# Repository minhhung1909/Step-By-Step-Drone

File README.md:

### 🚀 Day 1: Power Management Architecture & Schematic Design
* **Fixed & Verified Output Rails**: Finalized the power tree architecture for the 4-in-1 FOC ESC[cite: 1].
* **Buck Converter Stage (MP2359)**: Configured the step-down regulator to efficiently drop the main battery voltage down to a stable 5V rail.
* **LDO Linear Regulator Stage (MIC5219-3.3)**: Integrated the ultra-low noise LDO to convert 5V to 3.3V, ensuring a clean analog supply (`VDDA`) for the STM32G431 MCU and preventing FOC current-sensing noise.
* **Schematic Captures**: 
  * Configured proper bootstrapping components and decoupling/filtering capacitors.
  * Set up component attributes (such as DNP for optional feed-forward configurations) to keep the BOM clean for manufacturing.

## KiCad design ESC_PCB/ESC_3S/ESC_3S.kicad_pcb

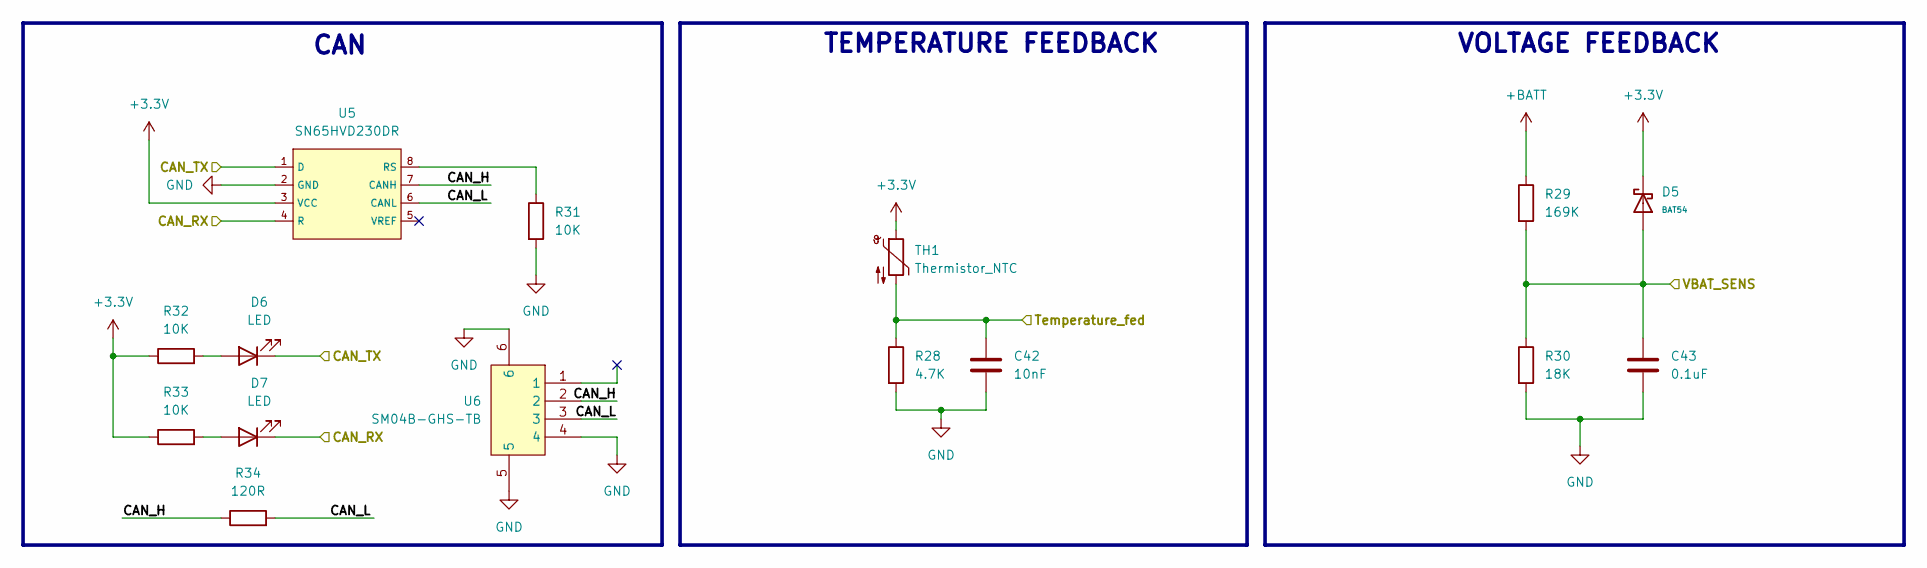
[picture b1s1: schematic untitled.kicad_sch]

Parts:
C42: 10nF; C_0603_1608Metric_Pad1.08x0.95mm_HandSolder
C43: 0.1uF; C_0603_1608Metric_Pad1.08x0.95mm_HandSolder
D5: BAT54; D_SOT-23; Part BAT54; LCSC C22466368
D6, D7: LED; LED_0603_1608Metric_Pad1.05x0.95mm_HandSolder
R28: 4.7K; R_0603_1608Metric_Pad0.98x0.95mm_HandSolder
R29: 169K; R_0603_1608Metric_Pad0.98x0.95mm_HandSolder
R30: 18K; R_0603_1608Metric_Pad0.98x0.95mm_HandSolder
R31, R32, R33: 10K; R_0603_1608Metric_Pad0.98x0.95mm_HandSolder
R34: 120R; R_0603_1608Metric_Pad0.98x0.95mm_HandSolder
TH1: Thermistor_NTC; R_Axial_DIN0204_L3.6mm_D1.6mm_P2.54mm_Vertical
U5: SN65HVD230DR; SOIC-8_L4.9-W3.9-P1.27-LS6.0-BL; Supply Voltage 3V~3.6V; Part SN65HVD230DR; LCSC C12084
U6: SM04B-GHS-TB; CONN-SMD_4P-P1.25_SM04B-GHS-TB-LF-SN; MPN SM04B-GHS-TB(LF)(SN); LCSC Part C189895

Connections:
+3.3V: D5.3, R32.1, R33.1, TH1.1, U5.3 (VCC); also elsewhere on the board
+BATT: R29.1; also elsewhere on the board
/Addition/CAN_H: R34.1, U5.7 (CANH), U6.2
/Addition/CAN_L: R34.2, U5.6 (CANL), U6.3
/Addition/CAN_RX: D7.1 (K), U5.4 (R); also elsewhere on the board
/Addition/CAN_TX: D6.1 (K), U5.1 (D); also elsewhere on the board
/Addition/Temperature_fed: C42.1, R28.1, TH1.2; also elsewhere on the board
/Addition/VBAT_SENS: C43.1, D5.1, R29.2, R30.1; also elsewhere on the board
GND: C42.2, C43.2, R28.2, R30.2, R31.2, U5.2 (GND), U6.4, U6.5, U6.6; also elsewhere on the board
unnamed: D6.2 (A), R32.2
unnamed: D7.2 (A), R33.2
unnamed: R31.1, U5.8 (RS)

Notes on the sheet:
VOLTAGE FEEDBACK
TEMPERATURE FEEDBACK
CAN

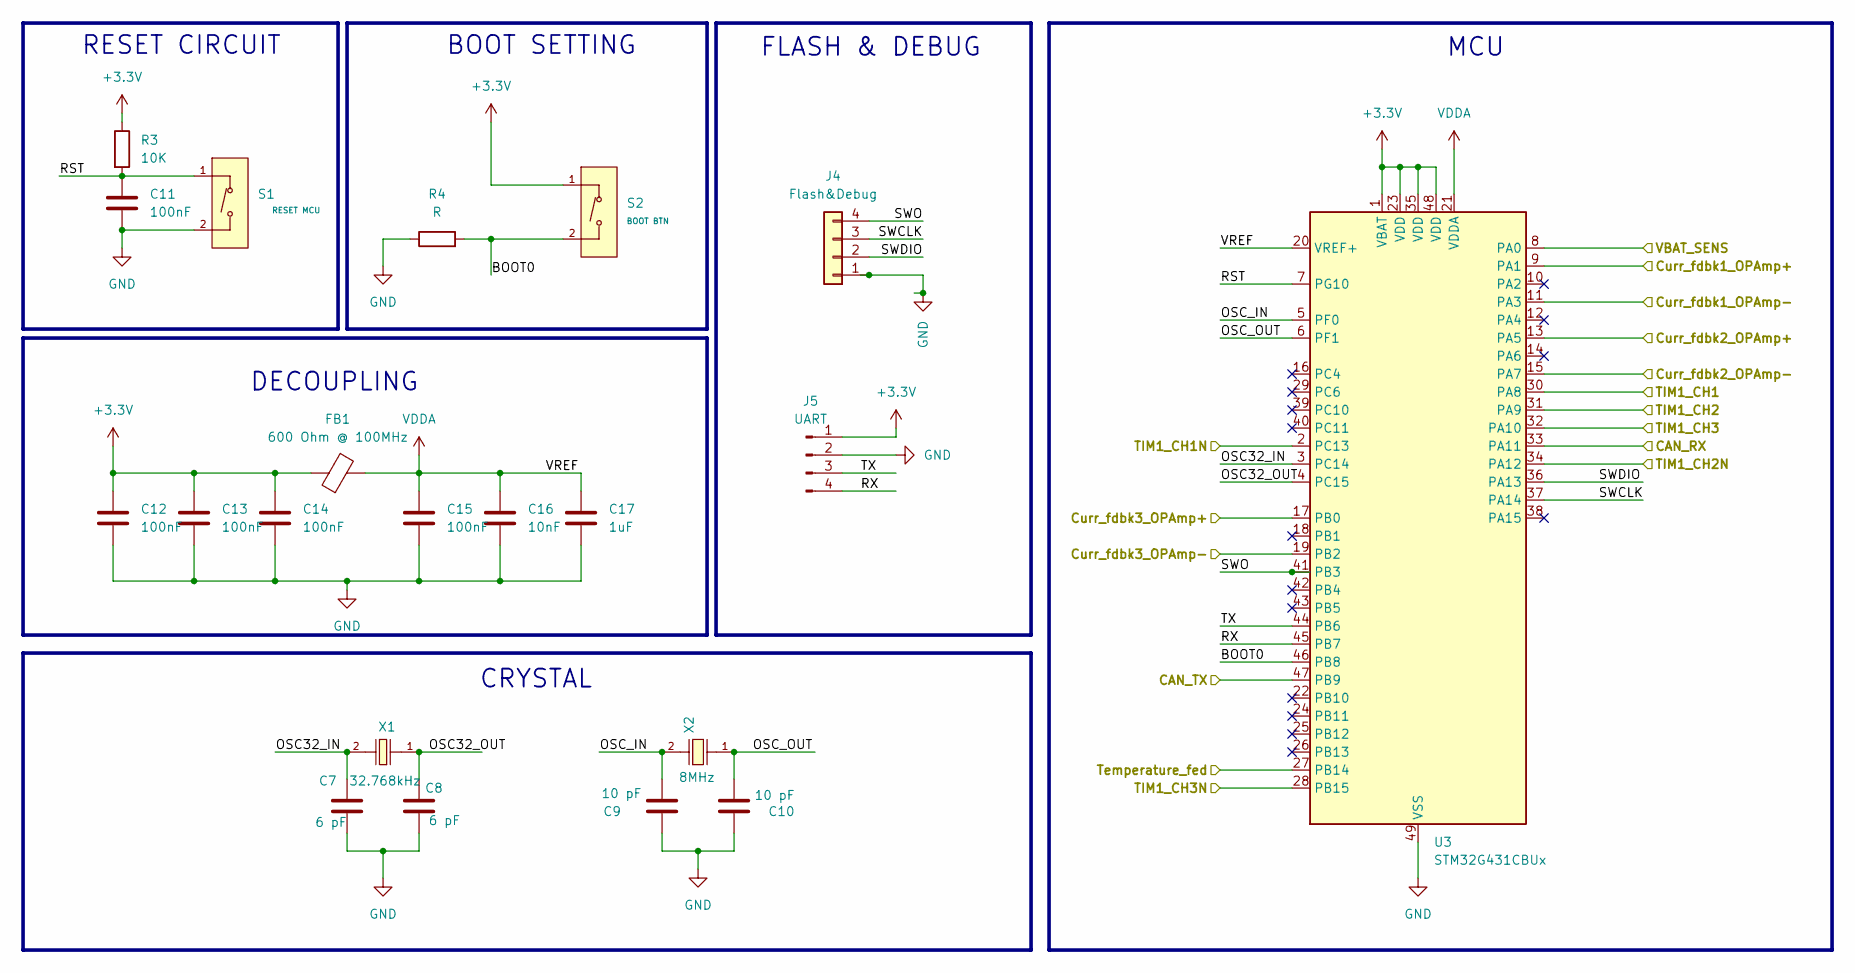
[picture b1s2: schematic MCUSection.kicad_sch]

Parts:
C7, C8: 6 pF; C_0603_1608Metric_Pad1.08x0.95mm_HandSolder
C9, C10: 10 pF; C_0603_1608Metric_Pad1.08x0.95mm_HandSolder
C11, C12, C13, C14, C15: 100nF; C_0603_1608Metric_Pad1.08x0.95mm_HandSolder
C16: 10nF; C_0603_1608Metric_Pad1.08x0.95mm_HandSolder
C17: 1uF; C_0603_1608Metric_Pad1.08x0.95mm_HandSolder
FB1: 600 Ohm @ 100MHz; L_0603_1608Metric_Pad1.05x0.95mm_HandSolder
J4: Flash&Debug; PinHeader_1x04_P1.27mm_Vertical
J5: UART; PinHeader_1x04_P2.54mm_Vertical
R3: 10K; R_0603_1608Metric_Pad0.98x0.95mm_HandSolder
R4: R; R_0603_1608Metric_Pad0.98x0.95mm_HandSolder
S1: RESET MCU; SW_TS-1088-AR02016; Voltage Rating (Dc) 12V; Part TS-1088-AR02016; LCSC C720477
S2: BOOT BTN; SW_TS-1088-AR02016; Voltage Rating (Dc) 12V; Part TS-1088-AR02016; LCSC C720477
U3: STM32G431CBUx; QFN-48-1EP_7x7mm_P0.5mm_EP5.6x5.6mm
X1: Q13FC1350000400; FC-135R_L3.2-W1.5; Frequency Tolerance ±20ppm; Part Q13FC13500004; LCSC C32346
X2: X50328MSB2GI; CRYSTAL-SMD_L5.0-W3.2; Frequency Tolerance ±10ppm; Part X50328MSB2GI; LCSC C115962

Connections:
+3.3V: C12.1, C13.1, C14.1, FB1.1, J5.1, R3.1, S2.1 (A), U3.1 (VBAT), U3.23 (VDD), U3.35 (VDD), U3.48 (VDD); also elsewhere on the board
/Addition/CAN_RX: U3.33 (PA11); also elsewhere on the board
/Addition/CAN_TX: U3.47 (PB9); also elsewhere on the board
/Addition/Temperature_fed: U3.27 (PB14); also elsewhere on the board
/Addition/VBAT_SENS: U3.8 (PA0); also elsewhere on the board
/Gate Driver and 3PH Inverter Bridge/Curr_fdbk1_OPAmp+: U3.9 (PA1); also elsewhere on the board
/Gate Driver and 3PH Inverter Bridge/Curr_fdbk2_OPAmp+: U3.13 (PA5); also elsewhere on the board
/Gate Driver and 3PH Inverter Bridge/Curr_fdbk3_OPAmp+: U3.17 (PB0); also elsewhere on the board
/Gate Driver and 3PH Inverter Bridge/TIM1_CH1: U3.30 (PA8); also elsewhere on the board
/Gate Driver and 3PH Inverter Bridge/TIM1_CH1N: U3.2 (PC13); also elsewhere on the board
/Gate Driver and 3PH Inverter Bridge/TIM1_CH2: U3.31 (PA9); also elsewhere on the board
/Gate Driver and 3PH Inverter Bridge/TIM1_CH2N: U3.34 (PA12); also elsewhere on the board
/Gate Driver and 3PH Inverter Bridge/TIM1_CH3: U3.32 (PA10); also elsewhere on the board
/Gate Driver and 3PH Inverter Bridge/TIM1_CH3N: U3.28 (PB15); also elsewhere on the board
/Gate Driver and 3PH Inverter Bridge/V_Shunt_1-: U3.11 (PA3); also elsewhere on the board
/Gate Driver and 3PH Inverter Bridge/V_Shunt_2-: U3.15 (PA7); also elsewhere on the board
/Gate Driver and 3PH Inverter Bridge/V_Shunt_3-: U3.19 (PB2); also elsewhere on the board
/MCU Section/BOOT0: R4.2, S2.2 (B), U3.46 (PB8)
/MCU Section/OSC32_IN: C7.1, U3.3 (PC14), X1.2
/MCU Section/OSC32_OUT: C8.1, U3.4 (PC15), X1.1
/MCU Section/OSC_IN: C9.1, U3.5 (PF0), X2.2
/MCU Section/OSC_OUT: C10.1, U3.6 (PF1), X2.1
/MCU Section/RST: C11.1, R3.2, S1.1 (A), U3.7 (PG10)
/MCU Section/RX: J5.4, U3.45 (PB7); also elsewhere on the board
/MCU Section/SWCLK: J4.3, U3.37 (PA14); also elsewhere on the board
/MCU Section/SWDIO: J4.2, U3.36 (PA13); also elsewhere on the board
/MCU Section/SWO: J4.4, U3.41 (PB3); also elsewhere on the board
/MCU Section/TX: J5.3, U3.44 (PB6); also elsewhere on the board
GND: C7.2, C8.2, C9.2, C10.2, C11.2, C12.2, C13.2, C14.2, C15.2, C16.2, C17.2, J4.1, J5.2, R4.1, S1.2 (B), U3.49 (VSS); also elsewhere on the board
VDDA: C15.1, C16.1, C17.1, FB1.2, U3.20 (VREF+), U3.21 (VDDA)

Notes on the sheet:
FLASH & DEBUG
DECOUPLING
RESET CIRCUIT
BOOT SETTING
CRYSTAL
MCU

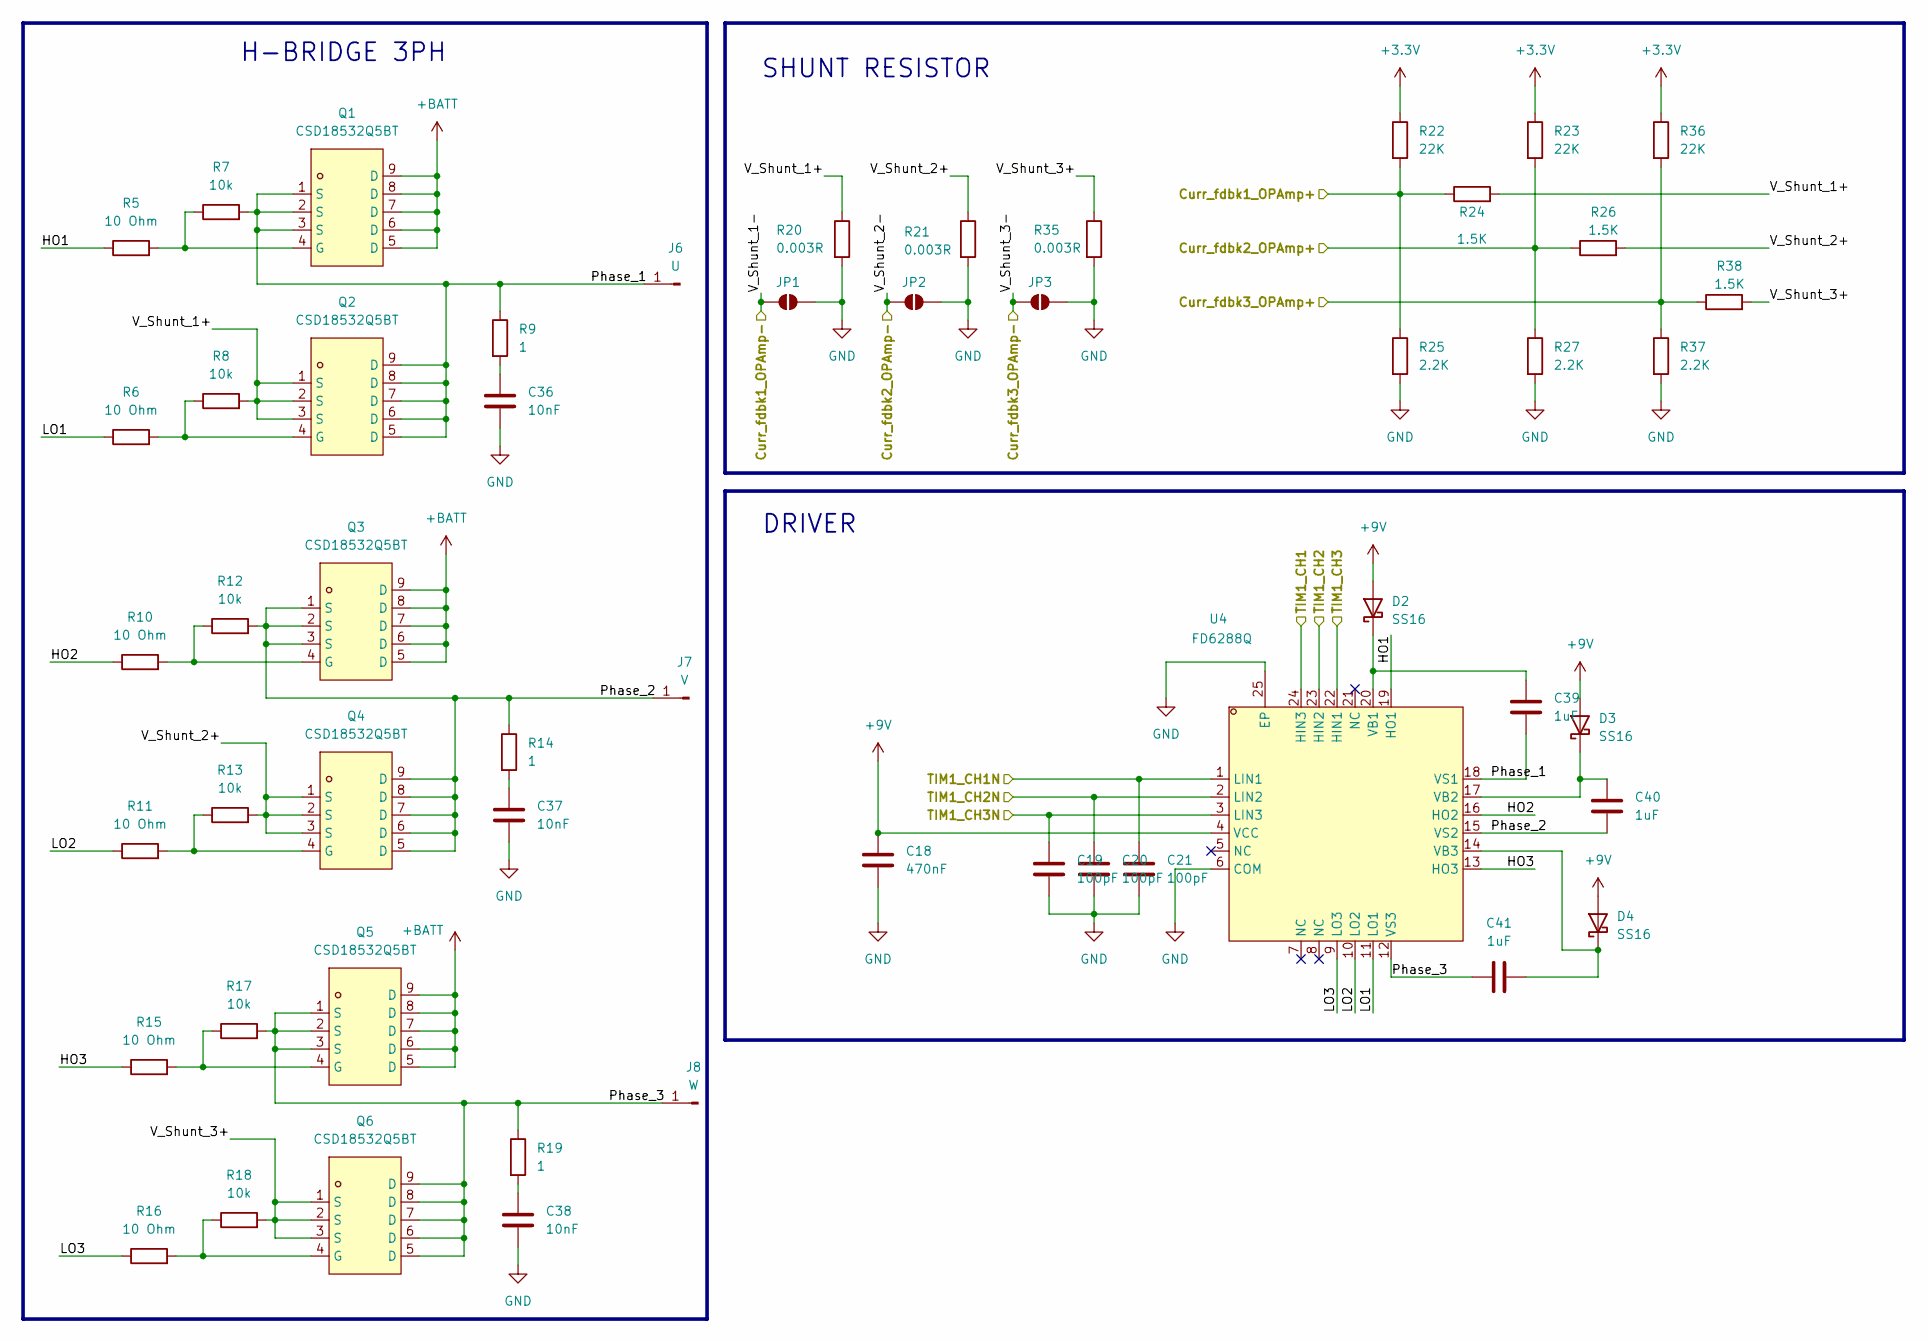
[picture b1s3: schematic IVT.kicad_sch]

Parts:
C18: 470nF; C_0603_1608Metric_Pad1.08x0.95mm_HandSolder
C19, C20, C21: 100pF; C_0603_1608Metric_Pad1.08x0.95mm_HandSolder
C36, C37, C38: 10nF; C_0603_1608Metric_Pad1.08x0.95mm_HandSolder
C39, C40, C41: 1uF; C_0603_1608Metric_Pad1.08x0.95mm_HandSolder
D2, D3, D4: SS16; D_SMA
J6: U; SolderWirePad_1x01_SMD_1x2mm
J7: V; SolderWirePad_1x01_SMD_1x2mm
J8: W; SolderWirePad_1x01_SMD_1x2mm
JP1, JP2, JP3: SolderJumper_2_Open; R_0402_1005Metric
Q1, Q2, Q3, Q4, Q5, Q6: CSD18532Q5BT; SON-8_L5.0-W6.0-P1.27-BL-1; MPN CSD18532Q5BT; LCSC Part C2876541
R5, R6, R10, R11, R15, R16: 10 Ohm; R_0603_1608Metric_Pad0.98x0.95mm_HandSolder
R7, R8, R12, R13, R17, R18: 10k; R_0603_1608Metric_Pad0.98x0.95mm_HandSolder
R9, R14, R19: 1; R_0603_1608Metric_Pad0.98x0.95mm_HandSolder
R20, R21, R35: 0.003R; R_2512_6332Metric_Pad1.40x3.35mm_HandSolder
R22, R23, R36: 22K; R_0603_1608Metric_Pad0.98x0.95mm_HandSolder
R24, R26, R38: 1.5K; R_0603_1608Metric_Pad0.98x0.95mm_HandSolder
R25, R27, R37: 2.2K; R_0603_1608Metric_Pad0.98x0.95mm_HandSolder
U4: FD6288Q; QFN-24_L4.0-W4.0-P0.50-BL-EP2.6; MPN FD6288Q; LCSC Part C328453

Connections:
+3.3V: R22.1, R23.1, R36.1; also elsewhere on the board
+9V: C18.1, D2.2 (A), D3.2 (A), D4.2 (A), U4.4 (VCC); also elsewhere on the board
+BATT: Q1.5 (D), Q1.6 (D), Q1.7 (D), Q1.8 (D), Q1.9 (D), Q3.5 (D), Q3.6 (D), Q3.7 (D), Q3.8 (D), Q3.9 (D), Q5.5 (D), Q5.6 (D), Q5.7 (D), Q5.8 (D), Q5.9 (D); also elsewhere on the board
/Gate Driver and 3PH Inverter Bridge/Curr_fdbk1_OPAmp+: R22.2, R24.1, R25.1; also elsewhere on the board
/Gate Driver and 3PH Inverter Bridge/Curr_fdbk2_OPAmp+: R23.2, R26.1, R27.1; also elsewhere on the board
/Gate Driver and 3PH Inverter Bridge/Curr_fdbk3_OPAmp+: R36.2, R37.1, R38.1; also elsewhere on the board
/Gate Driver and 3PH Inverter Bridge/HO1: R5.1, U4.19 (HO1)
/Gate Driver and 3PH Inverter Bridge/HO2: R10.1, U4.16 (HO2)
/Gate Driver and 3PH Inverter Bridge/HO3: R15.1, U4.13 (HO3)
/Gate Driver and 3PH Inverter Bridge/LO1: R6.1, U4.11 (LO1)
/Gate Driver and 3PH Inverter Bridge/LO2: R11.1, U4.10 (LO2)
/Gate Driver and 3PH Inverter Bridge/LO3: R16.1, U4.9 (LO3)
/Gate Driver and 3PH Inverter Bridge/Phase_1: C39.2, J6.1, Q1.1 (S), Q1.2 (S), Q1.3 (S), Q2.5 (D), Q2.6 (D), Q2.7 (D), Q2.8 (D), Q2.9 (D), R7.2, R9.1, U4.18 (VS1)
/Gate Driver and 3PH Inverter Bridge/Phase_2: C40.2, J7.1, Q3.1 (S), Q3.2 (S), Q3.3 (S), Q4.5 (D), Q4.6 (D), Q4.7 (D), Q4.8 (D), Q4.9 (D), R12.2, R14.1, U4.15 (VS2)
/Gate Driver and 3PH Inverter Bridge/Phase_3: C41.1, J8.1, Q5.1 (S), Q5.2 (S), Q5.3 (S), Q6.5 (D), Q6.6 (D), Q6.7 (D), Q6.8 (D), Q6.9 (D), R17.2, R19.1, U4.12 (VS3)
/Gate Driver and 3PH Inverter Bridge/TIM1_CH1: U4.24 (HIN3); also elsewhere on the board
/Gate Driver and 3PH Inverter Bridge/TIM1_CH1N: C21.1, U4.1 (LIN1); also elsewhere on the board
/Gate Driver and 3PH Inverter Bridge/TIM1_CH2: U4.23 (HIN2); also elsewhere on the board
/Gate Driver and 3PH Inverter Bridge/TIM1_CH2N: C20.1, U4.2 (LIN2); also elsewhere on the board
/Gate Driver and 3PH Inverter Bridge/TIM1_CH3: U4.22 (HIN1); also elsewhere on the board
/Gate Driver and 3PH Inverter Bridge/TIM1_CH3N: C19.1, U4.3 (LIN3); also elsewhere on the board
/Gate Driver and 3PH Inverter Bridge/V_Shunt_1+: Q2.1 (S), Q2.2 (S), Q2.3 (S), R8.2, R20.1, R24.2
/Gate Driver and 3PH Inverter Bridge/V_Shunt_1-: JP1.1 (A); also elsewhere on the board
/Gate Driver and 3PH Inverter Bridge/V_Shunt_2+: Q4.1 (S), Q4.2 (S), Q4.3 (S), R13.2, R21.1, R26.2
/Gate Driver and 3PH Inverter Bridge/V_Shunt_2-: JP2.1 (A); also elsewhere on the board
/Gate Driver and 3PH Inverter Bridge/V_Shunt_3+: Q6.1 (S), Q6.2 (S), Q6.3 (S), R18.2, R35.1, R38.2
/Gate Driver and 3PH Inverter Bridge/V_Shunt_3-: JP3.1 (A); also elsewhere on the board
GND: C18.2, C19.2, C20.2, C21.2, C36.2, C37.2, C38.2, JP1.2 (B), JP2.2 (B), JP3.2 (B), R20.2, R21.2, R25.2, R27.2, R35.2, R37.2, U4.6 (COM), U4.25 (EP); also elsewhere on the board
unnamed: C36.1, R9.2
unnamed: C37.1, R14.2
unnamed: C38.1, R19.2
unnamed: C39.1, D2.1 (K), U4.20 (VB1)
unnamed: C40.1, D3.1 (K), U4.17 (VB2)
unnamed: C41.2, D4.1 (K), U4.14 (VB3)
unnamed: Q1.4 (G), R5.2, R7.1
unnamed: Q2.4 (G), R6.2, R8.1
unnamed: Q3.4 (G), R10.2, R12.1
unnamed: Q4.4 (G), R11.2, R13.1
unnamed: Q5.4 (G), R15.2, R17.1
unnamed: Q6.4 (G), R16.2, R18.1

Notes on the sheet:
SHUNT RESISTOR
DRIVER
H-BRIDGE 3PH

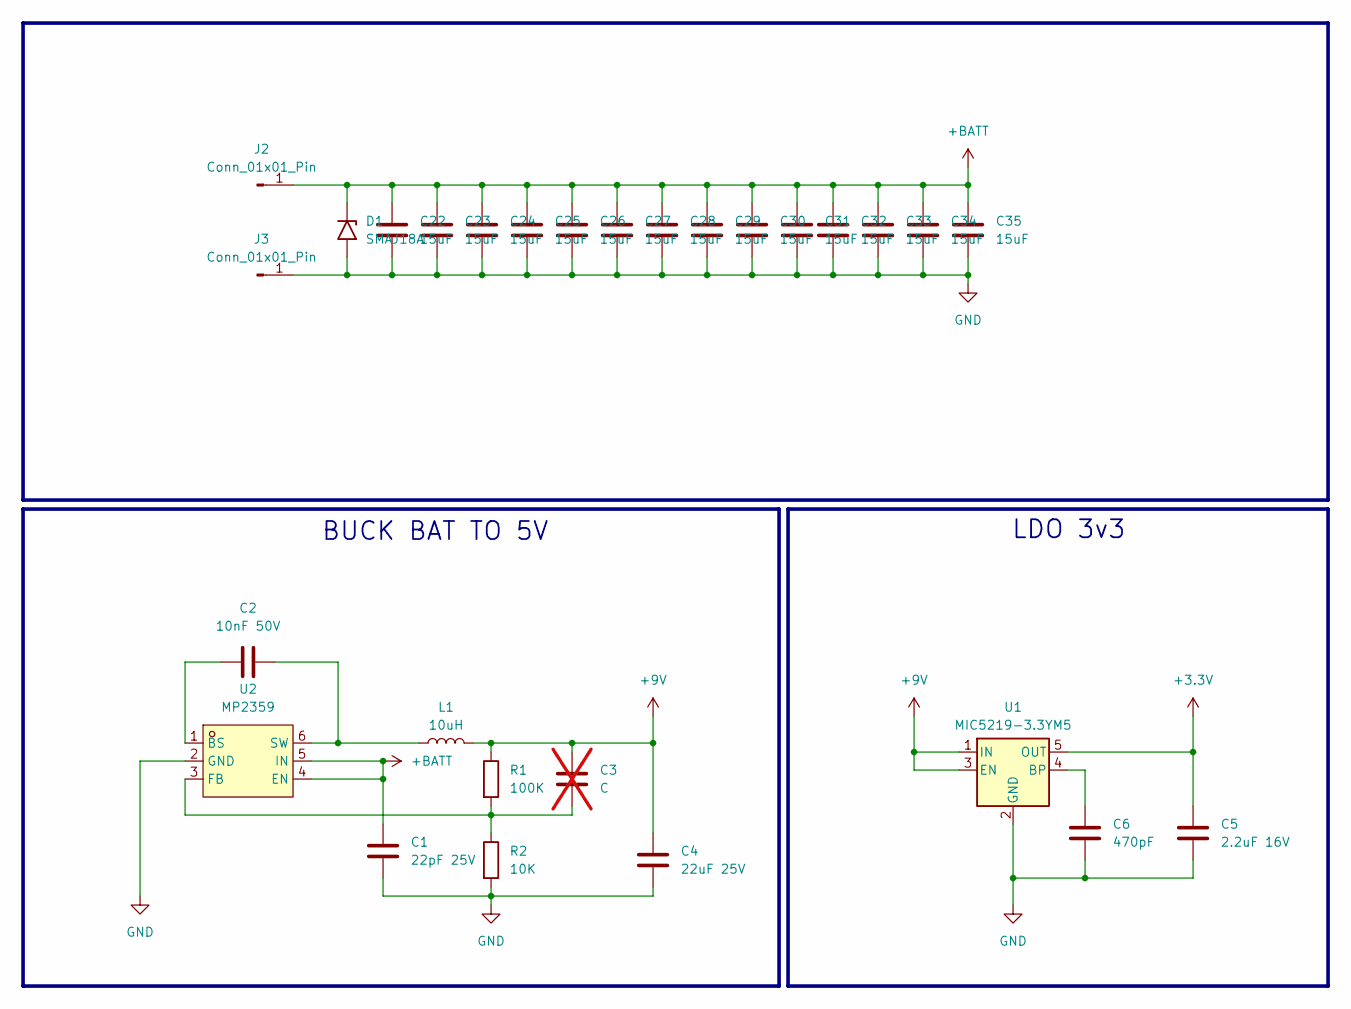
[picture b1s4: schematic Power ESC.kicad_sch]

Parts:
C1: 22pF 25V; C_0603_1608Metric_Pad1.08x0.95mm_HandSolder
C2: 10nF 50V; C_0603_1608Metric_Pad1.08x0.95mm_HandSolder
C3: C; C_0603_1608Metric_Pad1.08x0.95mm_HandSolder; not fitted
C4: 22uF 25V; C_0805_2012Metric_Pad1.18x1.45mm_HandSolder
C5: 2.2uF 16V; C_1206_3216Metric_Pad1.33x1.80mm_HandSolder
C6: 470pF; C_0603_1608Metric_Pad1.08x0.95mm_HandSolder
C22, C23, C24, C25, C26, C27, C28, C29, C30, C31, C32, C33, C34, C35: 15uF; C_0603_1608Metric_Pad1.08x0.95mm_HandSolder
D1: SMAJ18A; D_SMA_Handsoldering
J2, J3: Conn_01x01_Pin; SolderWire-0.25sqmm_1x01_D0.65mm_OD1.7mm
L1: 10uH; L_1206_3216Metric_Pad1.22x1.90mm_HandSolder
R1: 100K; R_0603_1608Metric_Pad0.98x0.95mm_HandSolder
R2: 10K; R_0603_1608Metric_Pad0.98x0.95mm_HandSolder
U1: MIC5219-3.3YM5; SOT-23-5
U2: MP2359; SOT-23-6_L2.9-W1.6-P0.95-LS2.8-BR; MPN MP2359DJ-LF-Z-MS; LCSC Part C30197555

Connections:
+3.3V: C6.1, U1.4 (BP); also elsewhere on the board
+9V: C3.1, C4.1, L1.2, R1.1, U1.1 (IN), U1.3 (EN); also elsewhere on the board
+BATT: C1.1, C22.1, C23.1, C24.1, C25.1, C26.1, C27.1, C28.1, C29.1, C30.1, C31.1, C32.1, C33.1, C34.1, C35.1, D1.1 (A1), J2.1, U2.4 (EN), U2.5 (IN); also elsewhere on the board
GND: C1.2, C4.2, C5.2, C6.2, C22.2, C23.2, C24.2, C25.2, C26.2, C27.2, C28.2, C29.2, C30.2, C31.2, C32.2, C33.2, C34.2, C35.2, D1.2 (A2), J3.1, R2.2, U1.2 (GND), U2.2 (GND); also elsewhere on the board
unnamed: C5.1, U1.5 (OUT)
unnamed 54: C2.2, L1.1, U2.6 (SW); also elsewhere on the board
unnamed: C2.1, U2.1 (BS)
unnamed: C3.2, R1.2, R2.1, U2.3 (FB)

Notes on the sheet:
LDO 3v3
BUCK BAT TO 5V

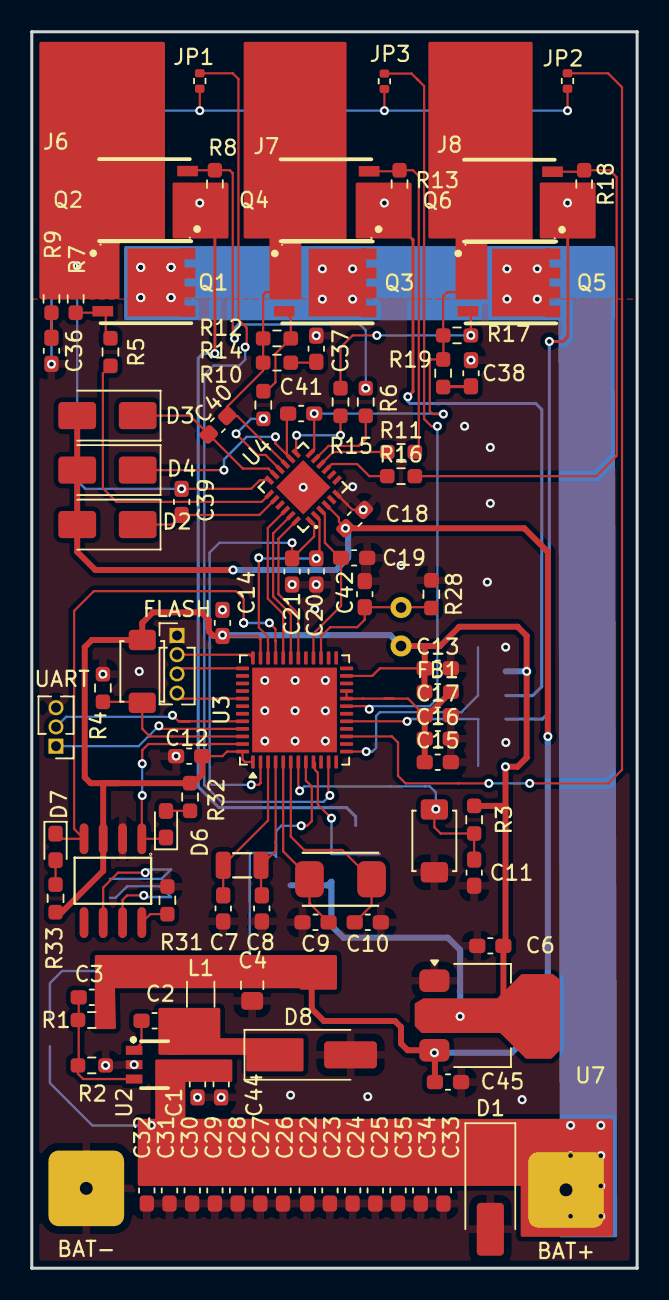
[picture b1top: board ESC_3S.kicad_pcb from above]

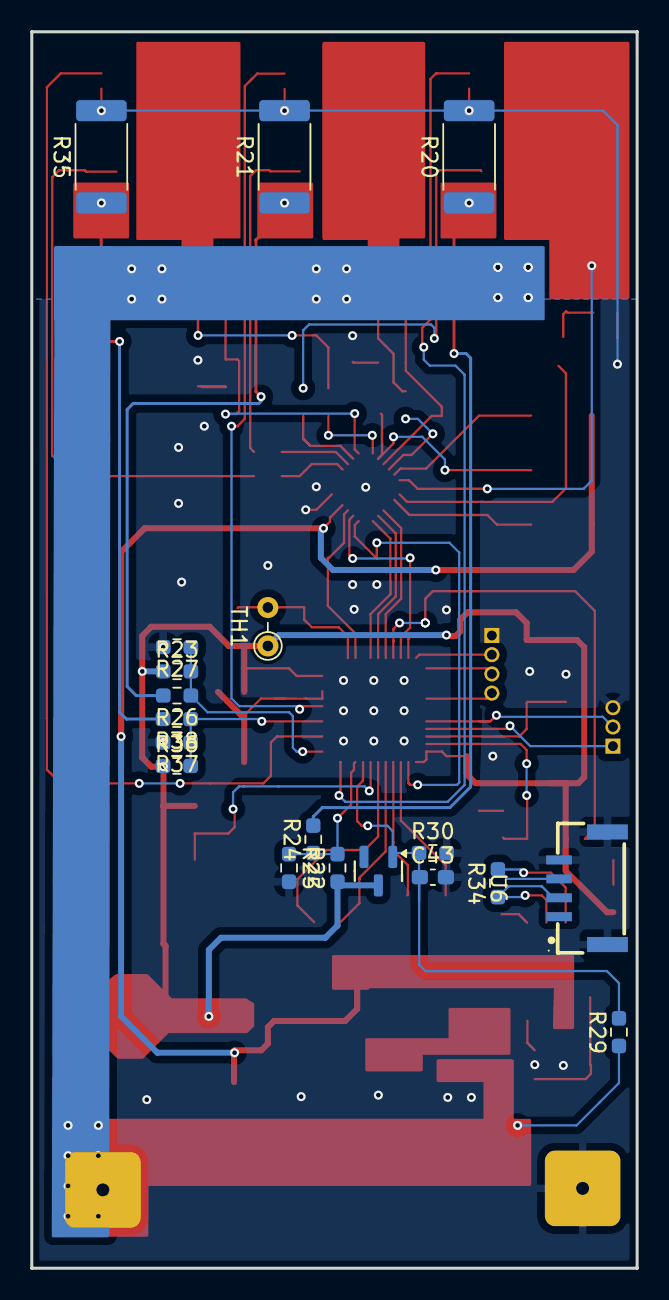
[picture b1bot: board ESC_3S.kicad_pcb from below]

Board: 2 copper layers, 40.0 x 81.7 mm, 119 parts (19 on the bottom side), 64 nets.

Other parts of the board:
BAT+: Conn_01x01_Pin; SolderWire-0.25sqmm_1x01_D0.65mm_OD1.7mm
BAT-: Conn_01x01_Pin; SolderWire-0.25sqmm_1x01_D0.65mm_OD1.7mm
C44: 100nF 25V; C_0603_1608Metric_Pad1.08x0.95mm_HandSolder
C45: 100nF; C_0603_1608Metric_Pad1.08x0.95mm_HandSolder
D8: SS34; D_SMA_Handsoldering
FLASH: Flash&Debug; PinHeader_1x04_P1.27mm_Vertical
U7: LD1117S33TR_SOT223; SOT-223-3_TabPin2
UART: UART; PinHeader_1x03_P1.27mm_Vertical

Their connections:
+3.3V: U7.2 (VO); also elsewhere on the board
+9V: C45.1, U7.3 (VI); also elsewhere on the board
+BATT: BAT+.1, C44.1; also elsewhere on the board
/MCU Section/RX: UART.1; also elsewhere on the board
/MCU Section/SWCLK: FLASH.3; also elsewhere on the board
/MCU Section/SWDIO: FLASH.2; also elsewhere on the board
/MCU Section/SWO: FLASH.4; also elsewhere on the board
/MCU Section/TX: UART.2; also elsewhere on the board
GND: BAT-.1, C44.2, C45.2, D8.2 (A), FLASH.1, U7.1 (GND), UART.3; also elsewhere on the board
unnamed 54: D8.1 (K); also elsewhere on the board

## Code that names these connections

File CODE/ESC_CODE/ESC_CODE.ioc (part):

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Mcu.Name=STM32G431C(6-8-B)Ux
Mcu.Package=UFQFPN48
Mcu.UserName=STM32G431CBUx
PA0.GPIOParameters=GPIO_Label
PA0.GPIO_Label=VBAT_SENS
PA0.Mode=IN1-Single-Ended
PA0.Signal=ADC1_IN1
PA1.Mode=standalone Internally connected_IO
PA1.Signal=OPAMP1_VINP
PA10.Signal=S_TIM1_CH3
PA11.Mode=FDCAN_Activate
PA11.Signal=FDCAN1_RX
PA12.Mode=PWM Generation2 CH2 CH2N
PA12.Signal=TIM1_CH2N
PA13.Mode=Trace_Asynchronous_SW
PA13.Signal=SYS_JTMS-SWDIO
PA14.Mode=Trace_Asynchronous_SW
PA14.Signal=SYS_JTCK-SWCLK
PA3.Mode=standalone Internally connected_IO
PA3.Signal=OPAMP1_VINM0
PA5.Mode=standalone Internally connected_IO
PA5.Signal=OPAMP2_VINM0
PA7.Mode=standalone Internally connected_IO
PA7.Signal=OPAMP2_VINP
PA8.Signal=S_TIM1_CH1
PA9.Signal=S_TIM1_CH2
PB0.Mode=standalone Internally connected_IO
PB0.Signal=OPAMP3_VINP
PB15.Mode=PWM Generation3 CH3 CH3N
PB15.Signal=TIM1_CH3N
PB2.Mode=standalone Internally connected_IO
PB2.Signal=OPAMP3_VINM0
PB3.Mode=Trace_Asynchronous_SW
PB3.Signal=SYS_JTDO-SWO
PB6.Mode=Asynchronous
PB6.Signal=USART1_TX
PB7.Mode=Asynchronous
PB7.Signal=USART1_RX
PB9.Mode=FDCAN_Activate
PB9.Signal=FDCAN1_TX
PC13.Mode=PWM Generation1 CH1 CH1N
PC13.Signal=TIM1_CH1N
PC14-OSC32_IN.Mode=LSE-External-Oscillator
PC14-OSC32_IN.Signal=RCC_OSC32_IN
PC15-OSC32_OUT.Mode=LSE-External-Oscillator
PC15-OSC32_OUT.Signal=RCC_OSC32_OUT
PF0-OSC_IN.Mode=HSE-External-Oscillator
PF0-OSC_IN.Signal=RCC_OSC_IN
PF1-OSC_OUT.Mode=HSE-External-Oscillator
PF1-OSC_OUT.Signal=RCC_OSC_OUT
RCC.HSE_VALUE=8000000
RCC.SYSCLKFreq_VALUE=16000000
board=custom

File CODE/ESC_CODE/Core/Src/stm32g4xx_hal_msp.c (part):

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
    __HAL_RCC_GPIOA_CLK_ENABLE();
    /**ADC1 GPIO Configuration
    PA0     ------> ADC1_IN1
    */
    GPIO_InitStruct.Pin = VBAT_SENS_Pin;
    GPIO_InitStruct.Mode = GPIO_MODE_ANALOG;
    GPIO_InitStruct.Pull = GPIO_NOPULL;
    HAL_GPIO_Init(VBAT_SENS_GPIO_Port, &GPIO_InitStruct);

    /* USER CODE BEGIN ADC1_MspInit 1 */

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    __HAL_RCC_ADC12_CLK_DISABLE();

    /**ADC1 GPIO Configuration
    PA0     ------> ADC1_IN1
    */
    HAL_GPIO_DeInit(VBAT_SENS_GPIO_Port, VBAT_SENS_Pin);

    /* USER CODE BEGIN ADC1_MspDeInit 1 */

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    __HAL_RCC_GPIOA_CLK_ENABLE();
    __HAL_RCC_GPIOB_CLK_ENABLE();
    /**FDCAN1 GPIO Configuration
    PA11     ------> FDCAN1_RX
    PB9     ------> FDCAN1_TX
    */
    GPIO_InitStruct.Pin = GPIO_PIN_11;
    GPIO_InitStruct.Mode = GPIO_MODE_AF_PP;
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    __HAL_RCC_FDCAN_CLK_DISABLE();

    /**FDCAN1 GPIO Configuration
    PA11     ------> FDCAN1_RX
    PB9     ------> FDCAN1_TX
    */
    HAL_GPIO_DeInit(GPIOA, GPIO_PIN_11);

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    __HAL_RCC_GPIOB_CLK_ENABLE();
    __HAL_RCC_GPIOA_CLK_ENABLE();
    /**TIM1 GPIO Configuration
    PC13     ------> TIM1_CH1N
    PB15     ------> TIM1_CH3N
    PA8     ------> TIM1_CH1
    PA9     ------> TIM1_CH2
    PA10     ------> TIM1_CH3
    PA12     ------> TIM1_CH2N
    */
    GPIO_InitStruct.Pin = GPIO_PIN_13;
    GPIO_InitStruct.Mode = GPIO_MODE_AF_PP;
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
    __HAL_RCC_GPIOB_CLK_ENABLE();
    /**USART1 GPIO Configuration
    PB6     ------> USART1_TX
    PB7     ------> USART1_RX
    */
    GPIO_InitStruct.Pin = GPIO_PIN_6|GPIO_PIN_7;
    GPIO_InitStruct.Mode = GPIO_MODE_AF_PP;
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    __HAL_RCC_USART1_CLK_DISABLE();

    /**USART1 GPIO Configuration
    PB6     ------> USART1_TX
    PB7     ------> USART1_RX
    */
    HAL_GPIO_DeInit(GPIOB, GPIO_PIN_6|GPIO_PIN_7);

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

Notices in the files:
CODE/ESC_CODE/Core/Src/stm32g4xx_hal_msp.c:
Copyright (c) 2026 STMicroelectronics.
All rights reserved.
This software is licensed under terms that can be found in the LICENSE file
